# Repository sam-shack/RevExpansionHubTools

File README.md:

# RevExpansionHubTools

## Serial capture tools
### IoNinja
https://www.ioninja.com/

### HddSoftware
https://www.hddsoftware.com

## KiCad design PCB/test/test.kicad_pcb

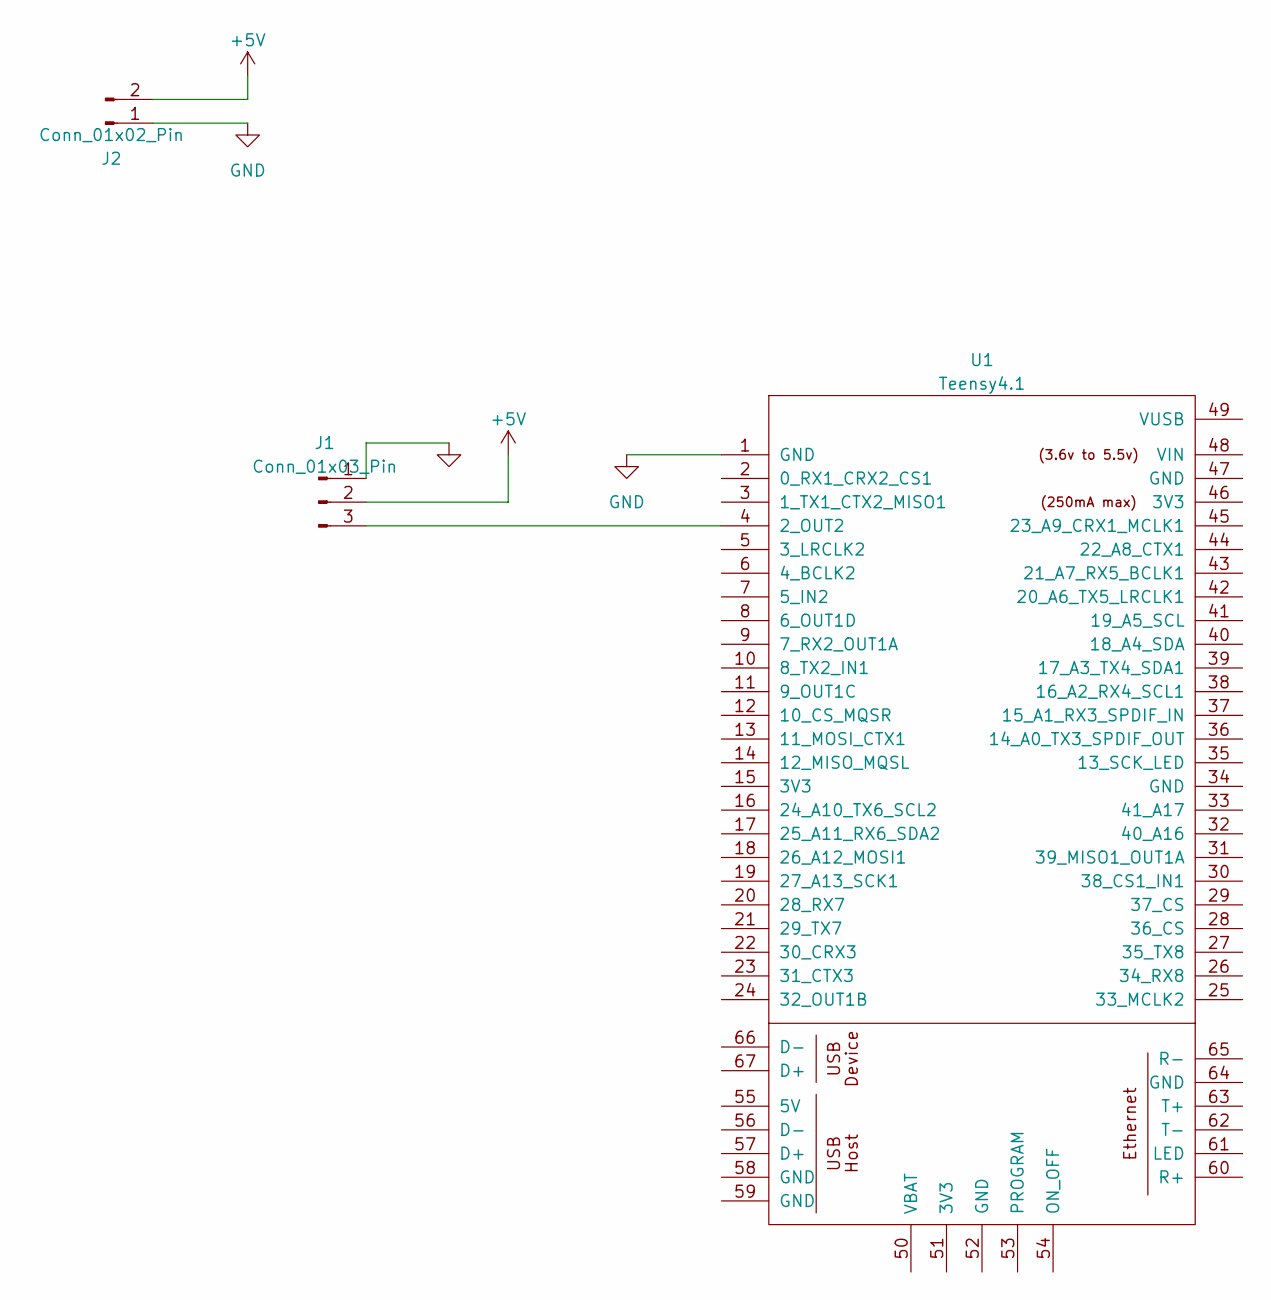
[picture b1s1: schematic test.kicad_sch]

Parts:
J1: Conn_01x03_Pin; PinHeader_1x03_P2.54mm_Horizontal
J2: Conn_01x02_Pin; PinHeader_1x02_P2.54mm_Horizontal
U1: Teensy4.1; Teensy41

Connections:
+5V: J1.2, J2.2
GND: J1.1, J2.1, U1.1 (GND)
unnamed: J1.3, U1.4 (2_OUT2)

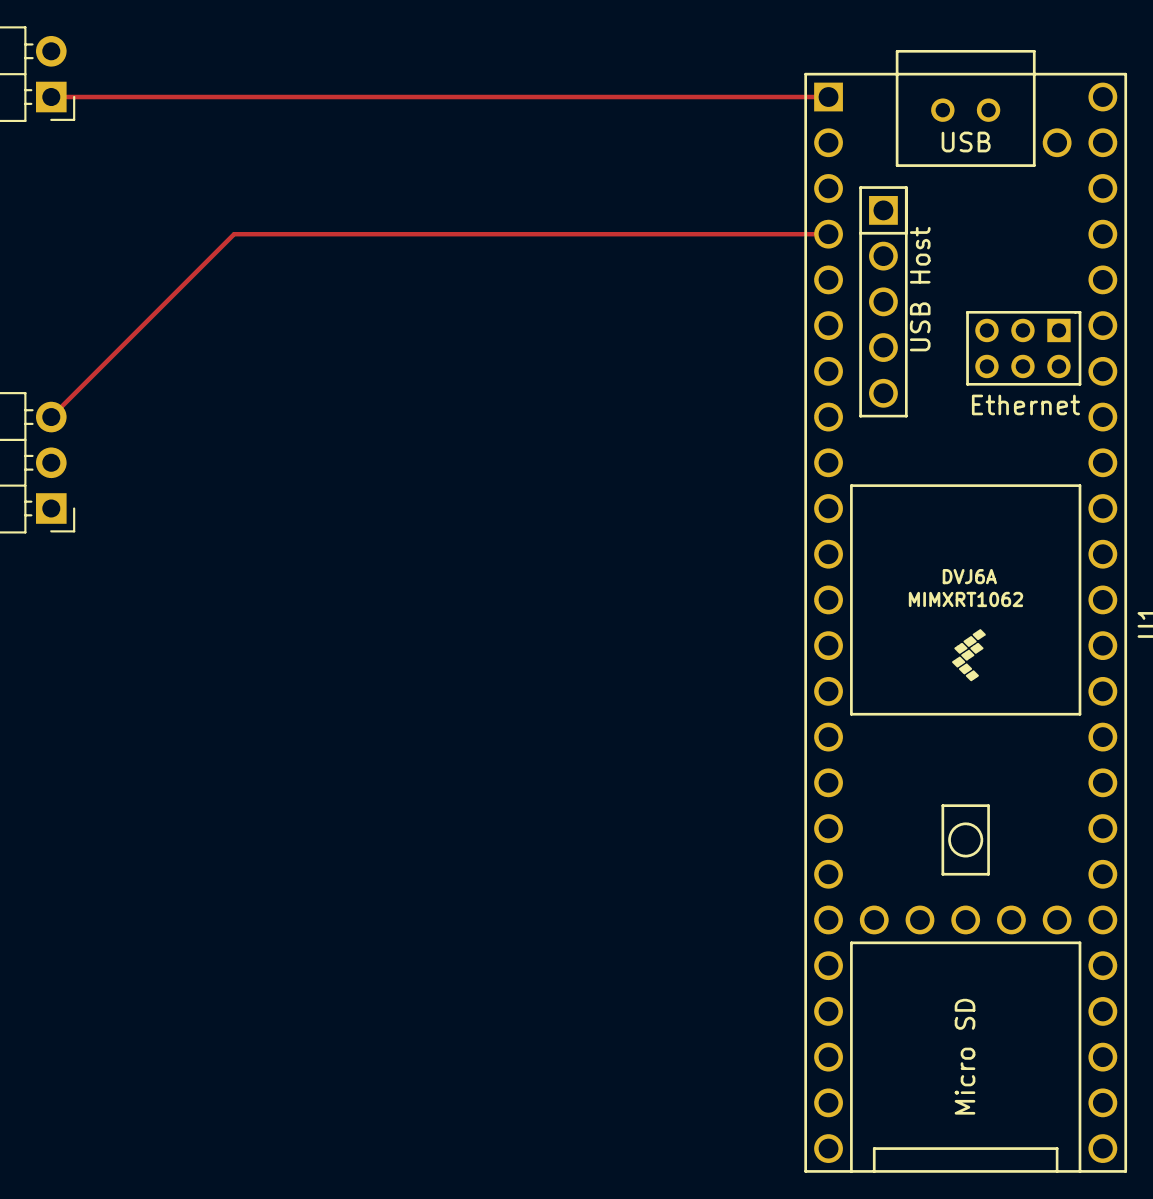
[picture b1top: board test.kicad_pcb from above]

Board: 2 copper layers, 3 parts (0 on the bottom side), 3 nets.

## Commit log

2023-04-30 Initial PCB schematic
2023-04-30 Initial python commit
2023-05-01 added PDFs
2023-06-04 added servo section
2023-06-06 updated doc
2023-06-07 Worked RS485 and serial
